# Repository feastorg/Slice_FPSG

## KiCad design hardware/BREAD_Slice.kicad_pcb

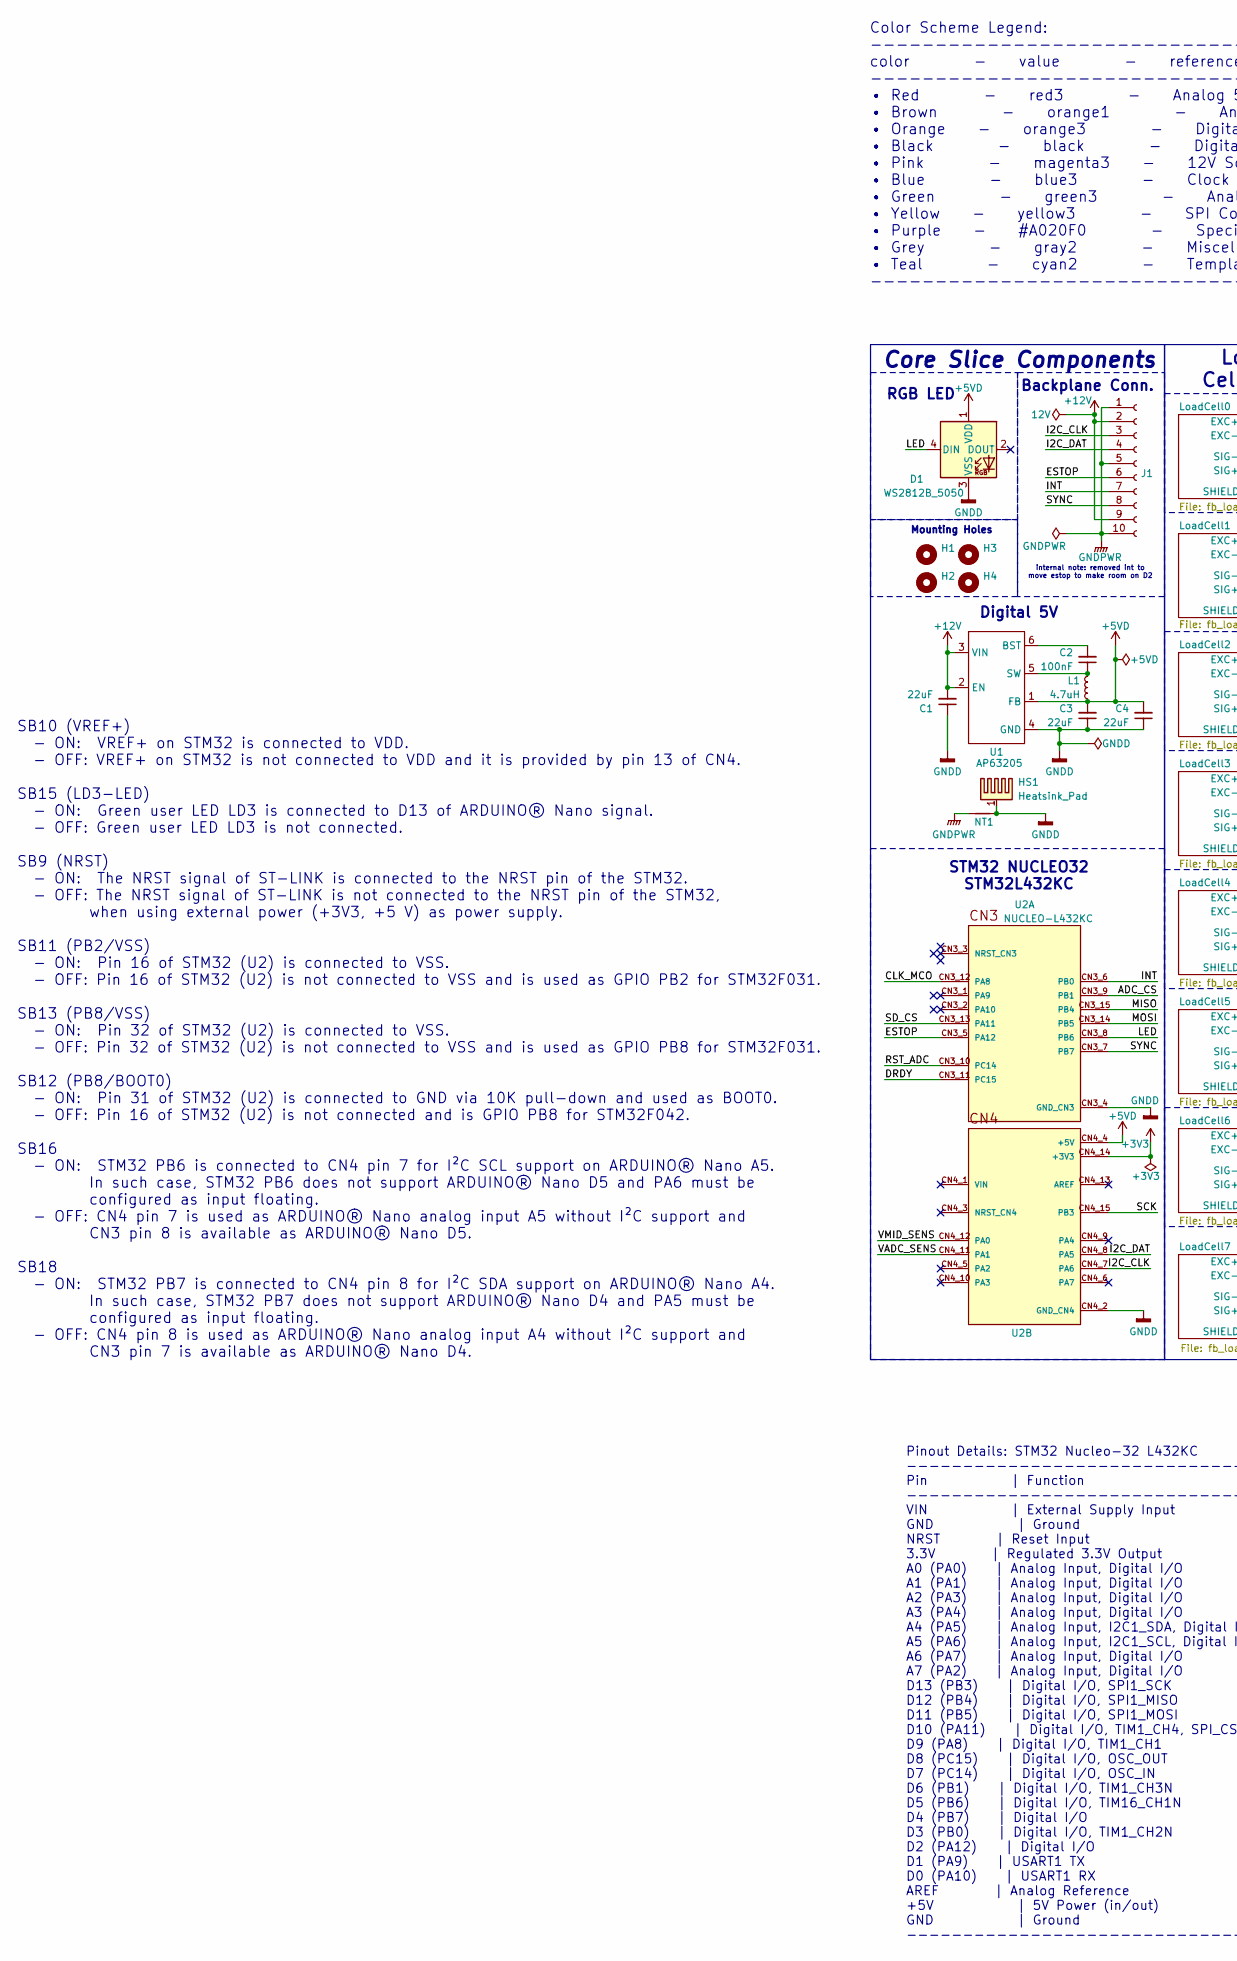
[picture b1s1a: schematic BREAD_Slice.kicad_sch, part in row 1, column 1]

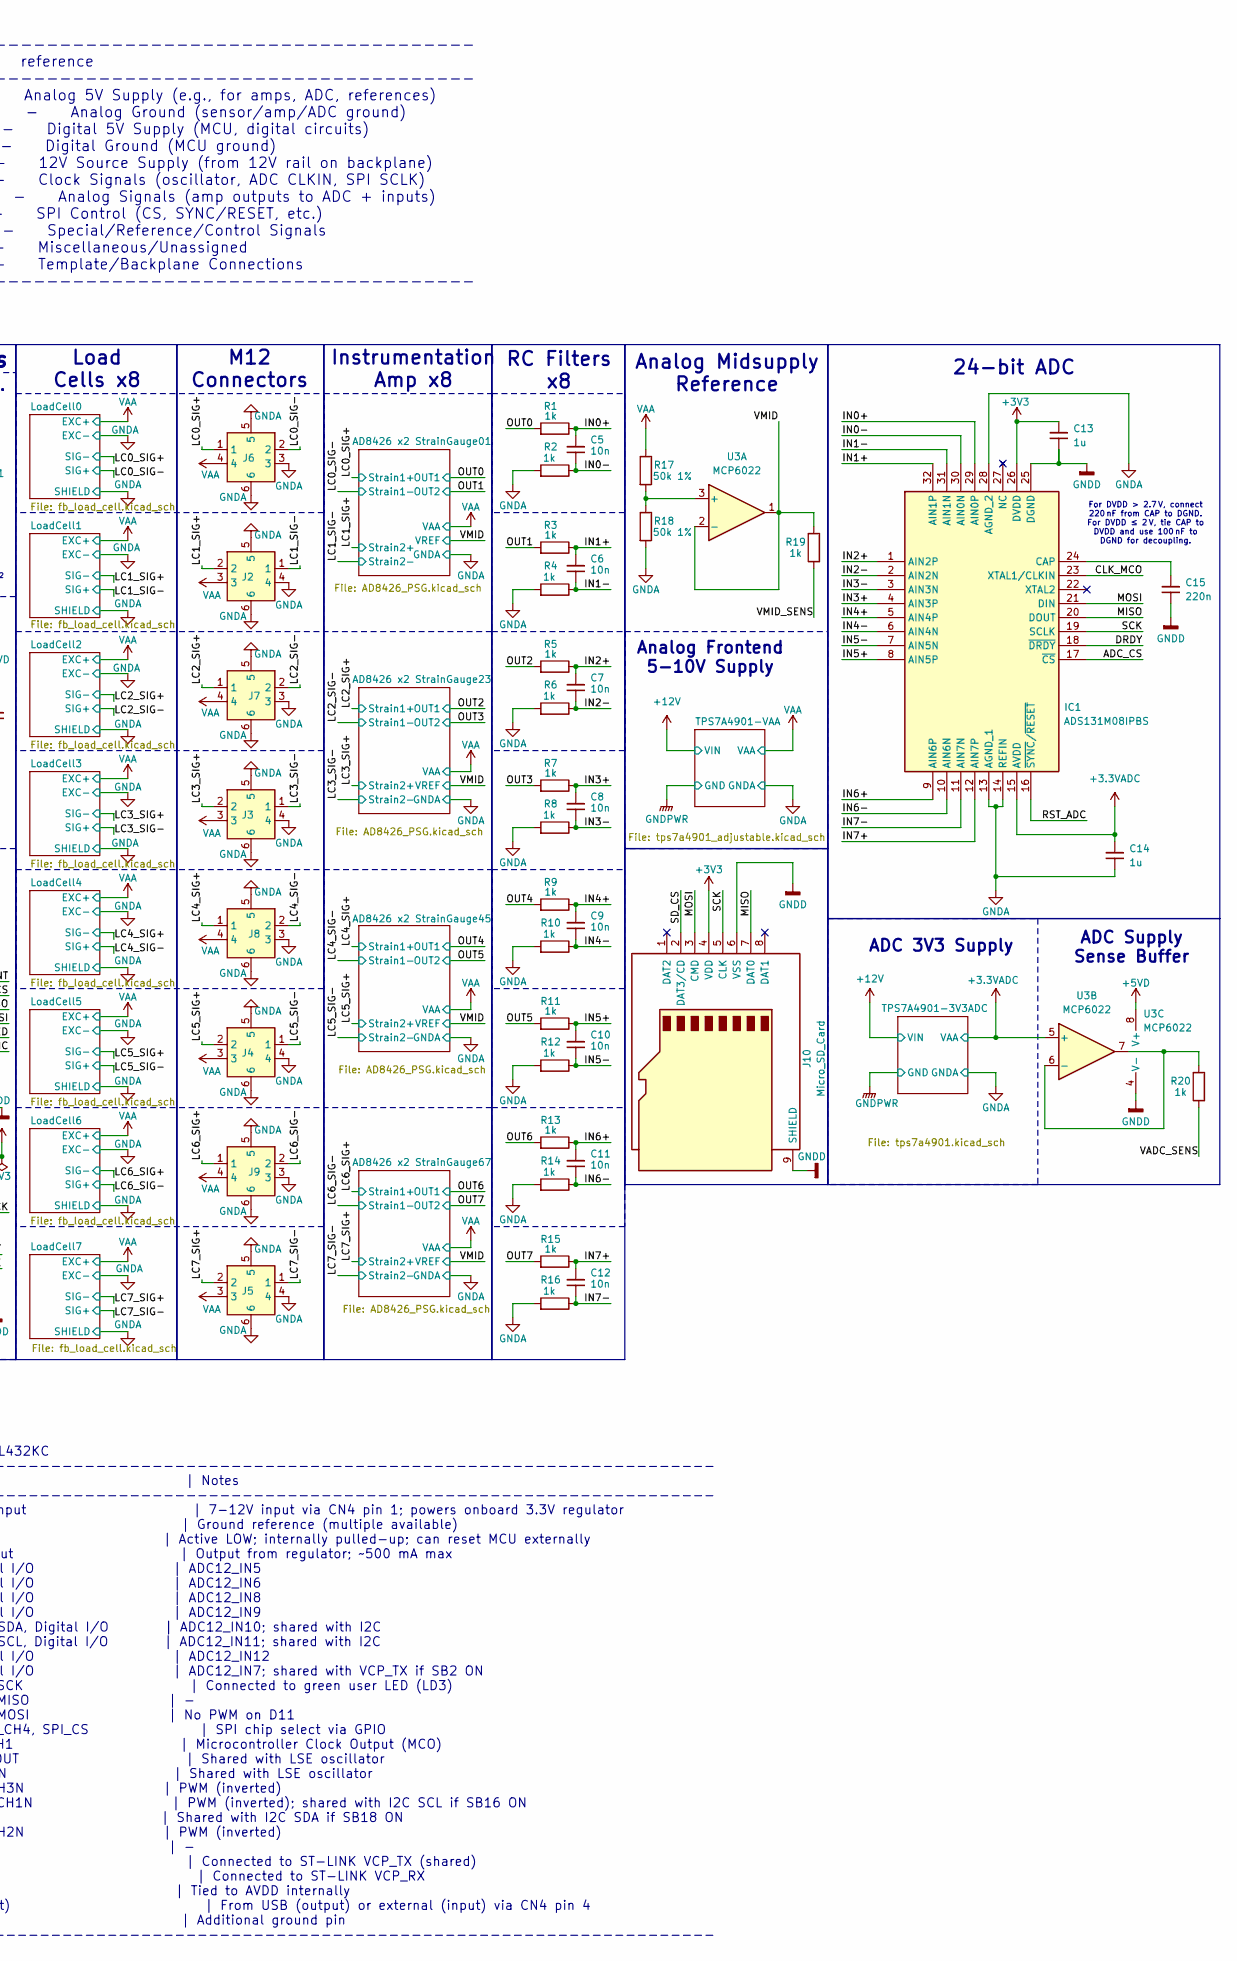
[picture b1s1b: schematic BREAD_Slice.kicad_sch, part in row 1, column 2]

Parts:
C1, C3, C4: 22uF; C_1206_3216Metric
C2: 100nF; C_1206_3216Metric
C5, C6, C7, C8, C9, C10, C11, C12: 10n; C_0805_2012Metric_Pad1.18x1.45mm_HandSolder
C13, C14: 1u; C_1206_3216Metric_Pad1.33x1.80mm_HandSolder
C15: 220n; C_1206_3216Metric_Pad1.33x1.80mm_HandSolder
D1: WS2812B_5050; WS2812-5050-4PIN
H1, H2, H3, H4: MountingHole; MountingHole_5mm
HS1: Heatsink_Pad; Thermal_Pad
IC1: ADS131M08IPBS; QFP50P700X700X120-32N; Mouser Part Number 595-ADS131M08IPBS
J1: Conn_01x10_Female; PinSocket_1x10_P2.54mm_Horizontal
J2, J3, J4, J5, J6, J7, J8, J9: 1439890; Mouser Part Number 651-1439890
J10: Micro_SD_Card; microSD_HC_Molex_47219-2001
L1: 4.7uH; L_1210_3225Metric
NT1: NetTie_2; NetTie-2_SMD_Pad2.0mm
R1, R2, R3, R4, R5, R6, R7, R8, R9, R10, R11, R12, R13, R14, R15, R16, R19, R20: 1k; R_0805_2012Metric_Pad1.20x1.40mm_HandSolder
R17, R18: 50k 1%; R_0805_2012Metric_Pad1.20x1.40mm_HandSolder
U1: AP63205; TSOT-23-6
U2: NUCLEO-L432KC; MODULE_NUCLEO-L432KC; PARTREV N/A
U3: MCP6022; SOIC-8_3.9x4.9mm_P1.27mm

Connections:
+3.3VADC: C14.2, IC1.15 (AVDD), U3.5 (+); also elsewhere on the board
+3V3: C13.2, IC1.26 (DVDD), J10.4 (VDD), U2.CN4_14 (+3V3)
+5VD: C3.2, C4.2, D1.1 (VDD), L1.2, U1.1 (FB), U2.CN4_4 (+5V), U3.8 (V+)
+12V: C1.2, J1.2, J1.9, U1.2 (EN), U1.3 (VIN); also elsewhere on the board
/ADC_CS: IC1.17 (~CS), U2.CN3_9 (PB1)
/CLK_MCO: IC1.23 (XTAL1/CLKIN), U2.CN3_12 (PA8)
/DRDY: IC1.18 (~DRDY), U2.CN3_11 (PC15)
/ESTOP: J1.6, U2.CN3_5 (PA12)
/I2C_CLK: J1.3, U2.CN4_7 (PA6)
/I2C_DAT: J1.4, U2.CN4_8 (PA5)
/IN0+: C5.2, IC1.29 (AIN0P), R1.1
/IN0-: C5.1, IC1.30 (AIN0N), R2.1
/IN1+: C6.2, IC1.32 (AIN1P), R3.1
/IN1-: C6.1, IC1.31 (AIN1N), R4.1
/IN2+: C7.2, IC1.1 (AIN2P), R5.1
/IN2-: C7.1, IC1.2 (AIN2N), R6.1
/IN3+: C8.2, IC1.4 (AIN3P), R7.1
/IN3-: C8.1, IC1.3 (AIN3N), R8.1
/IN4+: C9.2, IC1.5 (AIN4P), R9.1
/IN4-: C9.1, IC1.6 (AIN4N), R10.1
/IN5+: C10.2, IC1.8 (AIN5P), R11.1
/IN5-: C10.1, IC1.7 (AIN5N), R12.1
/IN6+: C11.2, IC1.9 (AIN6P), R13.1
/IN6-: C11.1, IC1.10 (AIN6N), R14.1
/IN7+: C12.2, IC1.12 (AIN7P), R15.1
/IN7-: C12.1, IC1.11 (AIN7N), R16.1
/INT: J1.7, U2.CN3_6 (PB0)
/LC0_SIG+: J6.1; also elsewhere on the board
/LC0_SIG-: J6.2; also elsewhere on the board
/LC1_SIG+: J2.2; also elsewhere on the board
/LC1_SIG-: J2.1; also elsewhere on the board
/LC2_SIG+: J7.1; also elsewhere on the board
/LC2_SIG-: J7.2; also elsewhere on the board
/LC3_SIG+: J3.2; also elsewhere on the board
/LC3_SIG-: J3.1; also elsewhere on the board
/LC4_SIG+: J8.1; also elsewhere on the board
/LC4_SIG-: J8.2; also elsewhere on the board
/LC5_SIG+: J4.2; also elsewhere on the board
/LC5_SIG-: J4.1; also elsewhere on the board
/LC6_SIG+: J9.1; also elsewhere on the board
/LC6_SIG-: J9.2; also elsewhere on the board
/LC7_SIG+: J5.2; also elsewhere on the board
/LC7_SIG-: J5.1; also elsewhere on the board
/LED: D1.4 (DIN), U2.CN3_8 (PB6)
/MISO: IC1.20 (DOUT), J10.7 (DAT0), U2.CN3_15 (PB4)
/MOSI: IC1.21 (DIN), J10.3 (CMD), U2.CN3_14 (PB5)
/OUT0: R1.2; also elsewhere on the board
/OUT1: R3.2; also elsewhere on the board
/OUT2: R5.2; also elsewhere on the board
/OUT3: R7.2; also elsewhere on the board
/OUT4: R9.2; also elsewhere on the board
/OUT5: R11.2; also elsewhere on the board
/OUT6: R13.2; also elsewhere on the board
/OUT7: R15.2; also elsewhere on the board
/RST_ADC: IC1.16 (~SYNC/~RESET), U2.CN3_10 (PC14)
/SCK: IC1.19 (SCLK), J10.5 (CLK), U2.CN4_15 (PB3)
/SD_CS: J10.2 (DAT3/CD), U2.CN3_13 (PA11)
/SYNC: J1.8, U2.CN3_7 (PB7)
/VADC_SENS: R20.2, U2.CN4_11 (PA1)
/VMID: R19.1, U3.1, U3.2 (-); also elsewhere on the board
/VMID_SENS: R19.2, U2.CN4_12 (PA0)
GNDA: C14.1, IC1.13 (AGND_1), IC1.14 (REFIN), IC1.28 (AGND_2), J2.4, J2.5, J2.6, J3.4, J3.5, J3.6, J4.4, J4.5, J4.6, J5.4, J5.5, J5.6, J6.3, J6.5, J6.6, J7.3, J7.5, J7.6, J8.3, J8.5, J8.6, J9.3, J9.5, J9.6, R2.2, R4.2, R6.2, R8.2, R10.2, R12.2, R14.2, R16.2, R18.2; also elsewhere on the board
GNDD: C1.1, C3.1, C4.1, C13.1, C15.1, D1.3 (VSS), HS1.1, IC1.25 (DGND), J10.6 (VSS), J10.9 (SHIELD), NT1.2, U1.4 (GND), U2.CN3_4 (GND_CN3), U2.CN4_2 (GND_CN4), U3.4 (V-)
GNDPWR: J1.1, J1.5, J1.10, NT1.1; also elsewhere on the board
unnamed: C15.2, IC1.24 (CAP)
unnamed: C2.2, U1.6 (BST)
unnamed: C2.1, L1.1, U1.5 (SW)
unnamed: R17.2, R18.1, U3.3 (+)
unnamed: R20.1, U3.6 (-), U3.7
VAA: J2.3, J3.3, J4.3, J5.3, J6.4, J7.4, J8.4, J9.4, R17.1; also elsewhere on the board

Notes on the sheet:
Digital 5V
RC Filters x8
Instrumentation Amp x8
Analog Frontend 5-10V Supply
RGB LED
Pinout Details: STM32 Nucleo-32 L432KC ------------------------------------------------------------------------------------- Pin | Function | Notes ------------------------------------------------------------------------------------- VIN | External Supply Input | 7-12V input via CN4 pin 1; powers o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
Load Cells x8
internal note: removed int to move estop to make room on D2
Color Scheme Legend: ---------------------------------------------------------- color - value - reference ---------------------------------------------------------- • Red - red3 - Analog 5V Supply (e.g., for amps, ADC, references) • Brown - orange1 - Analog Ground (sensor/amp/ADC ground) • Orange -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
Analog Midsupply Reference
SB10 (VREF+) - ON: VREF+ on STM32 is connected to VDD. - OFF: VREF+ on STM32 is not connected to VDD and it is provided by pin 13 of CN4. SB15 (LD3-LED) - ON: Green user LED LD3 is connected to D13 of ARDUINO® Nano signal. - OFF: Green user LED LD3 is not connected. SB9 (NRST) - ON: The NRST signal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
M12 Connectors
Core Slice Components
For DVDD > 2.7 V, connect 220 nF from CAP to DGND. For DVDD ≤ 2 V, tie CAP to DVDD and use 100 nF to DGND for decoupling.
ADC Supply Sense Buffer
STM32 NUCLEO32 STM32L432KC
24-bit ADC
ADC 3V3 Supply
Mounting Holes
Backplane Conn.

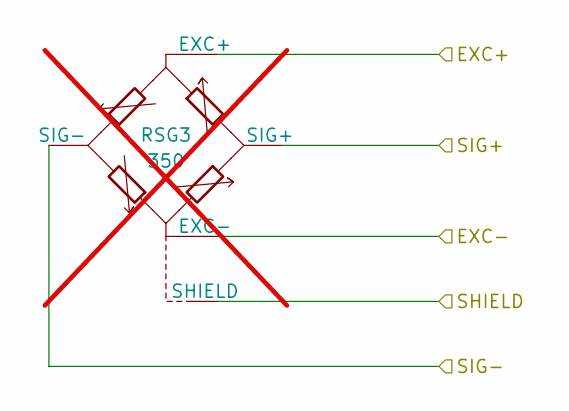
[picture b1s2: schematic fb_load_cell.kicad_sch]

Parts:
RSG3: 350; not fitted

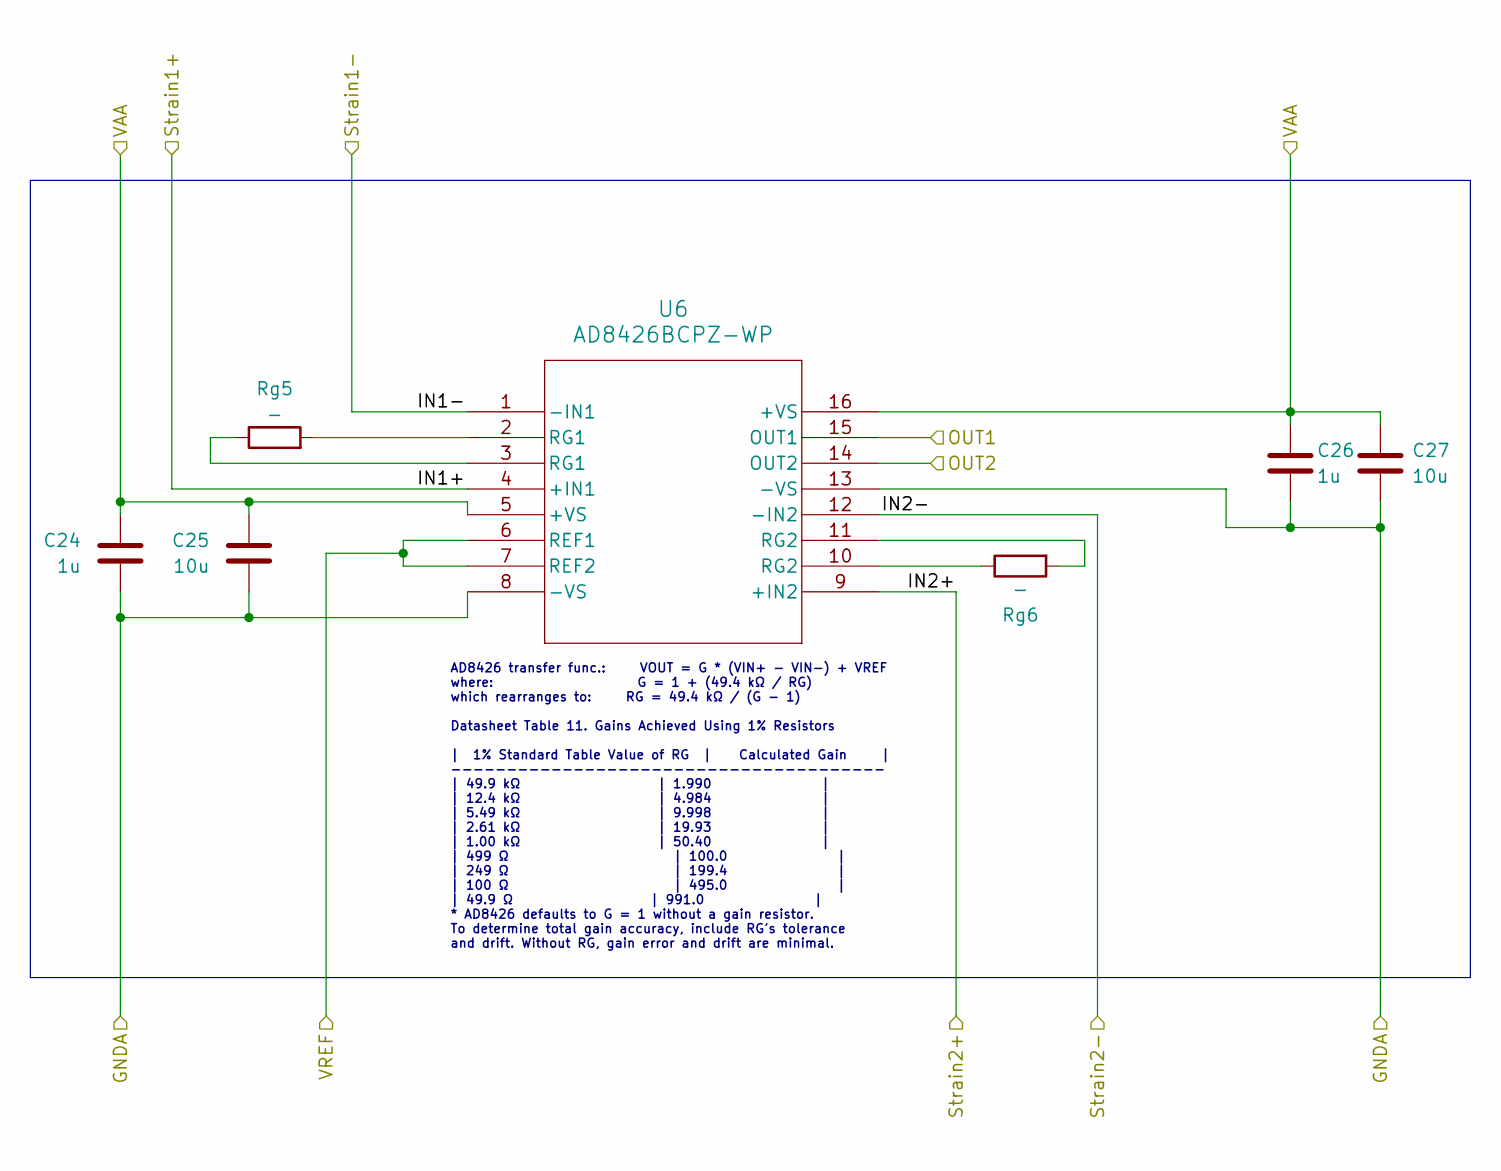
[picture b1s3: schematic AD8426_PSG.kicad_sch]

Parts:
C24, C26: 1u; C_0603_1608Metric_Pad1.08x0.95mm_HandSolder
C25, C27: 10u; C_0603_1608Metric_Pad1.08x0.95mm_HandSolder
Rg5, Rg6: -; R_0805_2012Metric_Pad1.20x1.40mm_HandSolder
U6: AD8426BCPZ-WP; CP_16_19_ADI

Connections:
/LC4_SIG+: U6.4 (+IN1); also elsewhere on the board
/LC4_SIG-: U6.1 (-IN1); also elsewhere on the board
/LC5_SIG+: U6.9 (+IN2); also elsewhere on the board
/LC5_SIG-: U6.12 (-IN2); also elsewhere on the board
/OUT4: U6.15 (OUT1); also elsewhere on the board
/OUT5: U6.14 (OUT2); also elsewhere on the board
/VMID: U6.6 (REF1), U6.7 (REF2); also elsewhere on the board
GNDA: C24.2, C25.2, C26.2, C27.2, U6.8 (-VS), U6.13 (-VS); also elsewhere on the board
unnamed: Rg5.1, U6.3 (RG1)
unnamed: Rg5.2, U6.2 (RG1)
unnamed: Rg6.1, U6.10 (RG2)
unnamed: Rg6.2, U6.11 (RG2)
VAA: C24.1, C25.1, C26.1, C27.1, U6.5 (+VS), U6.16 (+VS); also elsewhere on the board

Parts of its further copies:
C16, C18, C20, C22, C28, C30: 1u; C_0603_1608Metric_Pad1.08x0.95mm_HandSolder
C17, C19, C21, C23, C29, C31: 10u; C_0603_1608Metric_Pad1.08x0.95mm_HandSolder
Rg1, Rg2, Rg3, Rg4, Rg7, Rg8: -; R_0805_2012Metric_Pad1.20x1.40mm_HandSolder
U4, U5, U7: AD8426BCPZ-WP; CP_16_19_ADI

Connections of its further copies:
/LC0_SIG+: U4.4 (+IN1); also elsewhere on the board
/LC0_SIG-: U4.1 (-IN1); also elsewhere on the board
/LC1_SIG+: U4.9 (+IN2); also elsewhere on the board
/LC1_SIG-: U4.12 (-IN2); also elsewhere on the board
/LC2_SIG+: U5.4 (+IN1); also elsewhere on the board
/LC2_SIG-: U5.1 (-IN1); also elsewhere on the board
/LC3_SIG+: U5.9 (+IN2); also elsewhere on the board
/LC3_SIG-: U5.12 (-IN2); also elsewhere on the board
/LC6_SIG+: U7.4 (+IN1); also elsewhere on the board
/LC6_SIG-: U7.1 (-IN1); also elsewhere on the board
/LC7_SIG+: U7.9 (+IN2); also elsewhere on the board
/LC7_SIG-: U7.12 (-IN2); also elsewhere on the board
/OUT0: U4.15 (OUT1); also elsewhere on the board
/OUT1: U4.14 (OUT2); also elsewhere on the board
/OUT2: U5.15 (OUT1); also elsewhere on the board
/OUT3: U5.14 (OUT2); also elsewhere on the board
/OUT6: U7.15 (OUT1); also elsewhere on the board
/OUT7: U7.14 (OUT2); also elsewhere on the board
/VMID: U4.6 (REF1), U4.7 (REF2), U5.6 (REF1), U5.7 (REF2), U7.6 (REF1), U7.7 (REF2); also elsewhere on the board
GNDA: C16.2, C17.2, C18.2, C19.2, C20.2, C21.2, C22.2, C23.2, C28.2, C29.2, C30.2, C31.2, U4.8 (-VS), U4.13 (-VS), U5.8 (-VS), U5.13 (-VS), U7.8 (-VS), U7.13 (-VS); also elsewhere on the board
unnamed: Rg1.1, U4.3 (RG1)
unnamed: Rg1.2, U4.2 (RG1)
unnamed: Rg2.1, U4.10 (RG2)
unnamed: Rg2.2, U4.11 (RG2)
unnamed: Rg3.1, U5.3 (RG1)
unnamed: Rg3.2, U5.2 (RG1)
unnamed: Rg4.1, U5.10 (RG2)
unnamed: Rg4.2, U5.11 (RG2)
unnamed: Rg7.1, U7.3 (RG1)
unnamed: Rg7.2, U7.2 (RG1)
unnamed: Rg8.1, U7.10 (RG2)
unnamed: Rg8.2, U7.11 (RG2)
VAA: C16.1, C17.1, C18.1, C19.1, C20.1, C21.1, C22.1, C23.1, C28.1, C29.1, C30.1, C31.1, U4.5 (+VS), U4.16 (+VS), U5.5 (+VS), U5.16 (+VS), U7.5 (+VS), U7.16 (+VS); also elsewhere on the board

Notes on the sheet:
AD8426 transfer func.: VOUT = G * (VIN+ - VIN-) + VREF where: G = 1 + (49.4 kΩ / RG) which rearranges to: RG = 49.4 kΩ / (G - 1) Datasheet Table 11. Gains Achieved Using 1% Resistors | 1% Standard Table Value of RG | Calculated Gain | --------------------------------------- | 49.9 kΩ | 1.990 | | 12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

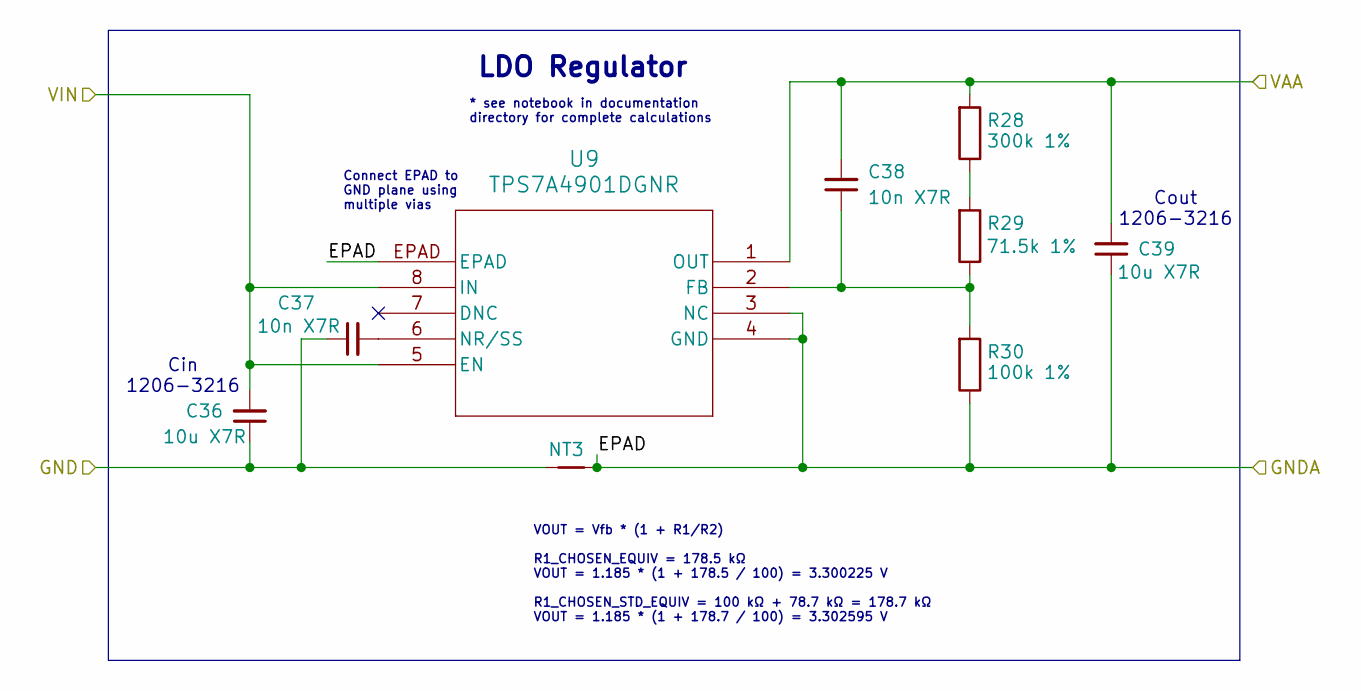
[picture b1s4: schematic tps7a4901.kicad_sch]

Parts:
C36, C39: 10u X7R; C_1206_3216Metric_Pad1.33x1.80mm_HandSolder
C37, C38: 10n X7R; C_0603_1608Metric_Pad1.08x0.95mm_HandSolder
NT3: NetTie_2; NetTie-2_SMD_Pad2.0mm
R28: 300k 1%; R_0805_2012Metric_Pad1.20x1.40mm_HandSolder
R29: 71.5k 1%; R_0805_2012Metric_Pad1.20x1.40mm_HandSolder
R30: 100k 1%; R_0805_2012Metric_Pad1.20x1.40mm_HandSolder
U9: TPS7A4901DGNR; DGN8_1P89X1P57

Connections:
+3.3VADC: C38.2, C39.2, R28.2, U9.1 (OUT); also elsewhere on the board
+12V: C36.2, U9.5 (EN), U9.8 (IN); also elsewhere on the board
GNDA: C39.1, NT3.2, R30.1, U9.3 (NC), U9.4 (GND), U9.EPAD; also elsewhere on the board
GNDPWR: C36.1, C37.1, NT3.1; also elsewhere on the board
unnamed: R28.1, R29.2
unnamed: C38.1, R29.1, R30.2, U9.2 (FB)
unnamed: C37.2, U9.6 (NR/SS)

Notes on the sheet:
Cin 1206-3216
LDO Regulator
Cout 1206-3216
* see notebook in documentation directory for complete calculations
VOUT = Vfb * (1 + R1/R2) R1_CHOSEN_EQUIV = 178.5 kΩ VOUT = 1.185 * (1 + 178.5 / 100) = 3.300225 V R1_CHOSEN_STD_EQUIV = 100 kΩ + 78.7 kΩ = 178.7 kΩ VOUT = 1.185 * (1 + 178.7 / 100) = 3.302595 V
Connect EPAD to GND plane using multiple vias

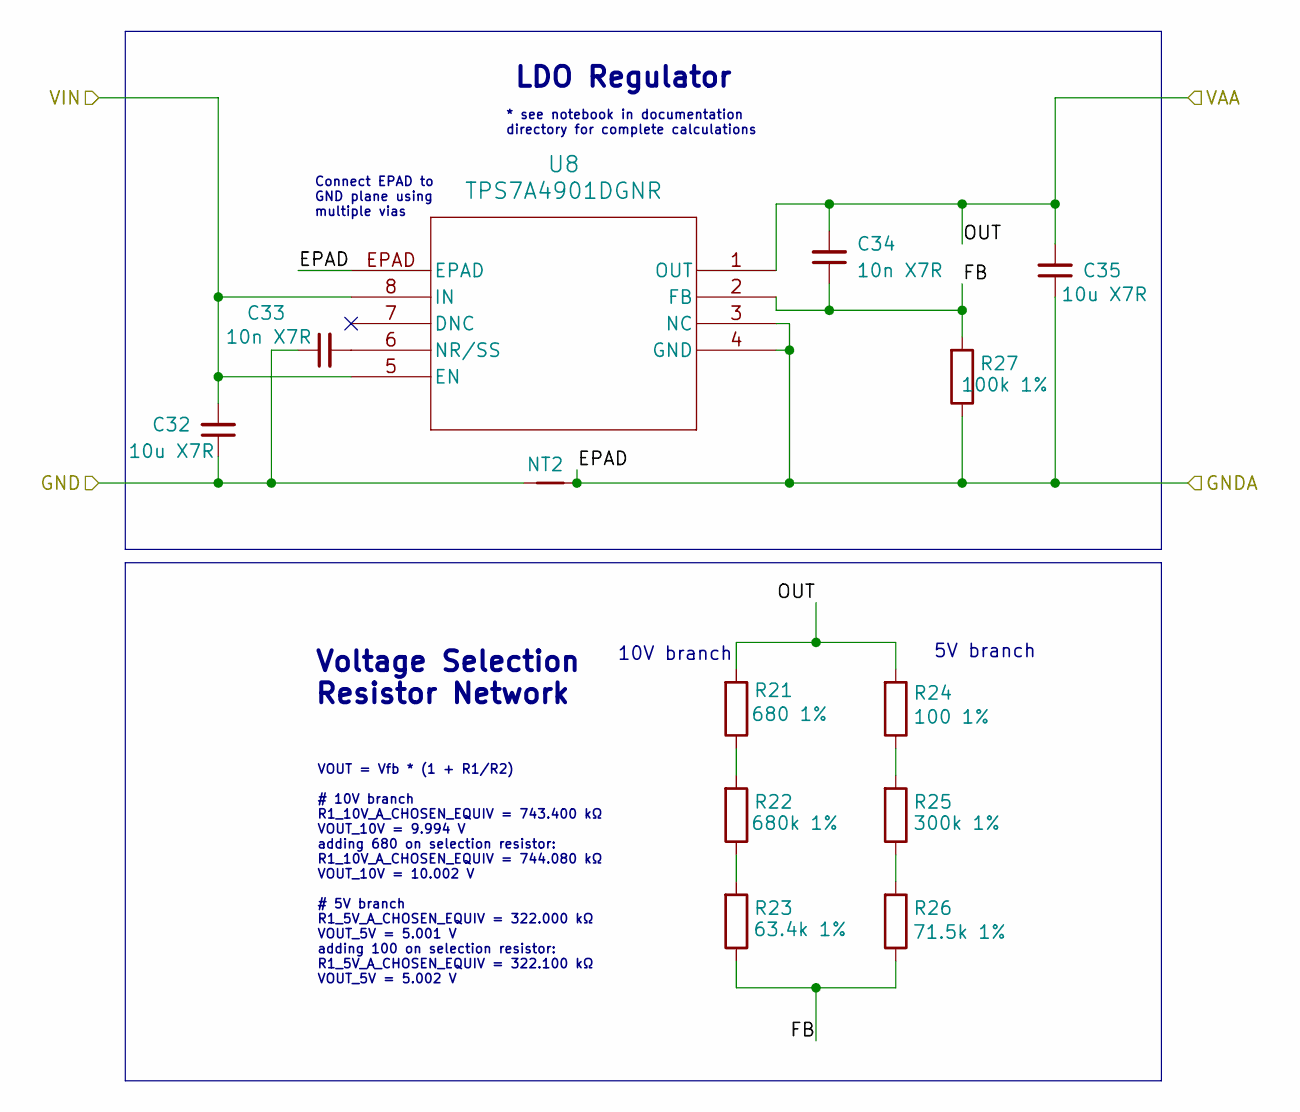
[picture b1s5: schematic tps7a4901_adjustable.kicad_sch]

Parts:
C32, C35: 10u X7R; C_1206_3216Metric_Pad1.33x1.80mm_HandSolder
C33, C34: 10n X7R; C_0603_1608Metric_Pad1.08x0.95mm_HandSolder
NT2: NetTie_2; NetTie-2_SMD_Pad2.0mm
R21: 680 1%; R_0805_2012Metric_Pad1.20x1.40mm_HandSolder
R22: 680k 1%; R_0805_2012Metric_Pad1.20x1.40mm_HandSolder
R23: 63.4k 1%; R_0805_2012Metric_Pad1.20x1.40mm_HandSolder
R24: 100 1%; R_0805_2012Metric_Pad1.20x1.40mm_HandSolder
R25: 300k 1%; R_0805_2012Metric_Pad1.20x1.40mm_HandSolder
R26: 71.5k 1%; R_0805_2012Metric_Pad1.20x1.40mm_HandSolder
R27: 100k 1%; R_0805_2012Metric_Pad1.20x1.40mm_HandSolder
U8: TPS7A4901DGNR; DGN8_1P89X1P57

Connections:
+12V: C32.2, U8.5 (EN), U8.8 (IN); also elsewhere on the board
/TPS7A4901-VAA/FB: C34.1, R23.1, R26.1, R27.2, U8.2 (FB)
GNDA: C35.1, NT2.2, R27.1, U8.3 (NC), U8.4 (GND), U8.EPAD; also elsewhere on the board
GNDPWR: C32.1, C33.1, NT2.1; also elsewhere on the board
unnamed: R21.1, R22.2
unnamed: R22.1, R23.2
unnamed: R24.1, R25.2
unnamed: R25.1, R26.2
unnamed: C33.2, U8.6 (NR/SS)
VAA: C34.2, C35.2, R21.2, R24.2, U8.1 (OUT); also elsewhere on the board

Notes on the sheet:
* see notebook in documentation directory for complete calculations
LDO Regulator
5V branch
VOUT = Vfb * (1 + R1/R2) # 10V branch R1_10V_A_CHOSEN_EQUIV = 743.400 kΩ VOUT_10V = 9.994 V adding 680 on selection resistor: R1_10V_A_CHOSEN_EQUIV = 744.080 kΩ VOUT_10V = 10.002 V # 5V branch R1_5V_A_CHOSEN_EQUIV = 322.000 kΩ VOUT_5V = 5.001 V adding 100 on selection resistor: R1_5V_A_CHOSEN_EQUIV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
Voltage Selection Resistor Network
10V branch
Connect EPAD to GND plane using multiple vias

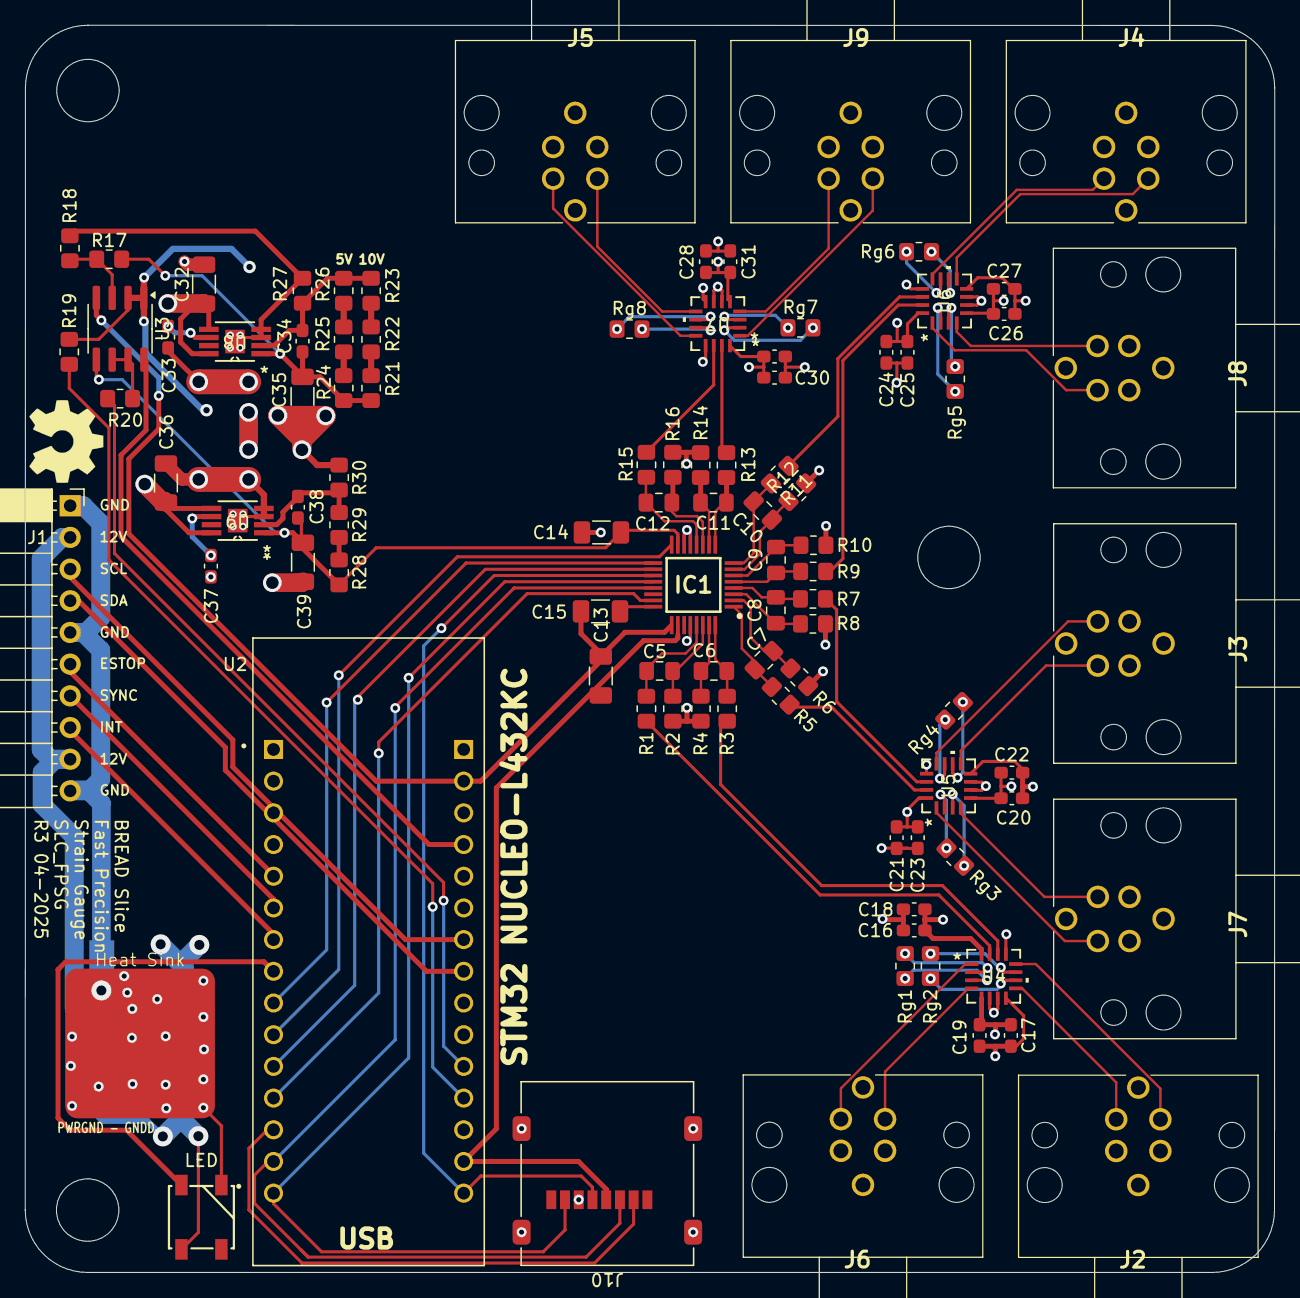
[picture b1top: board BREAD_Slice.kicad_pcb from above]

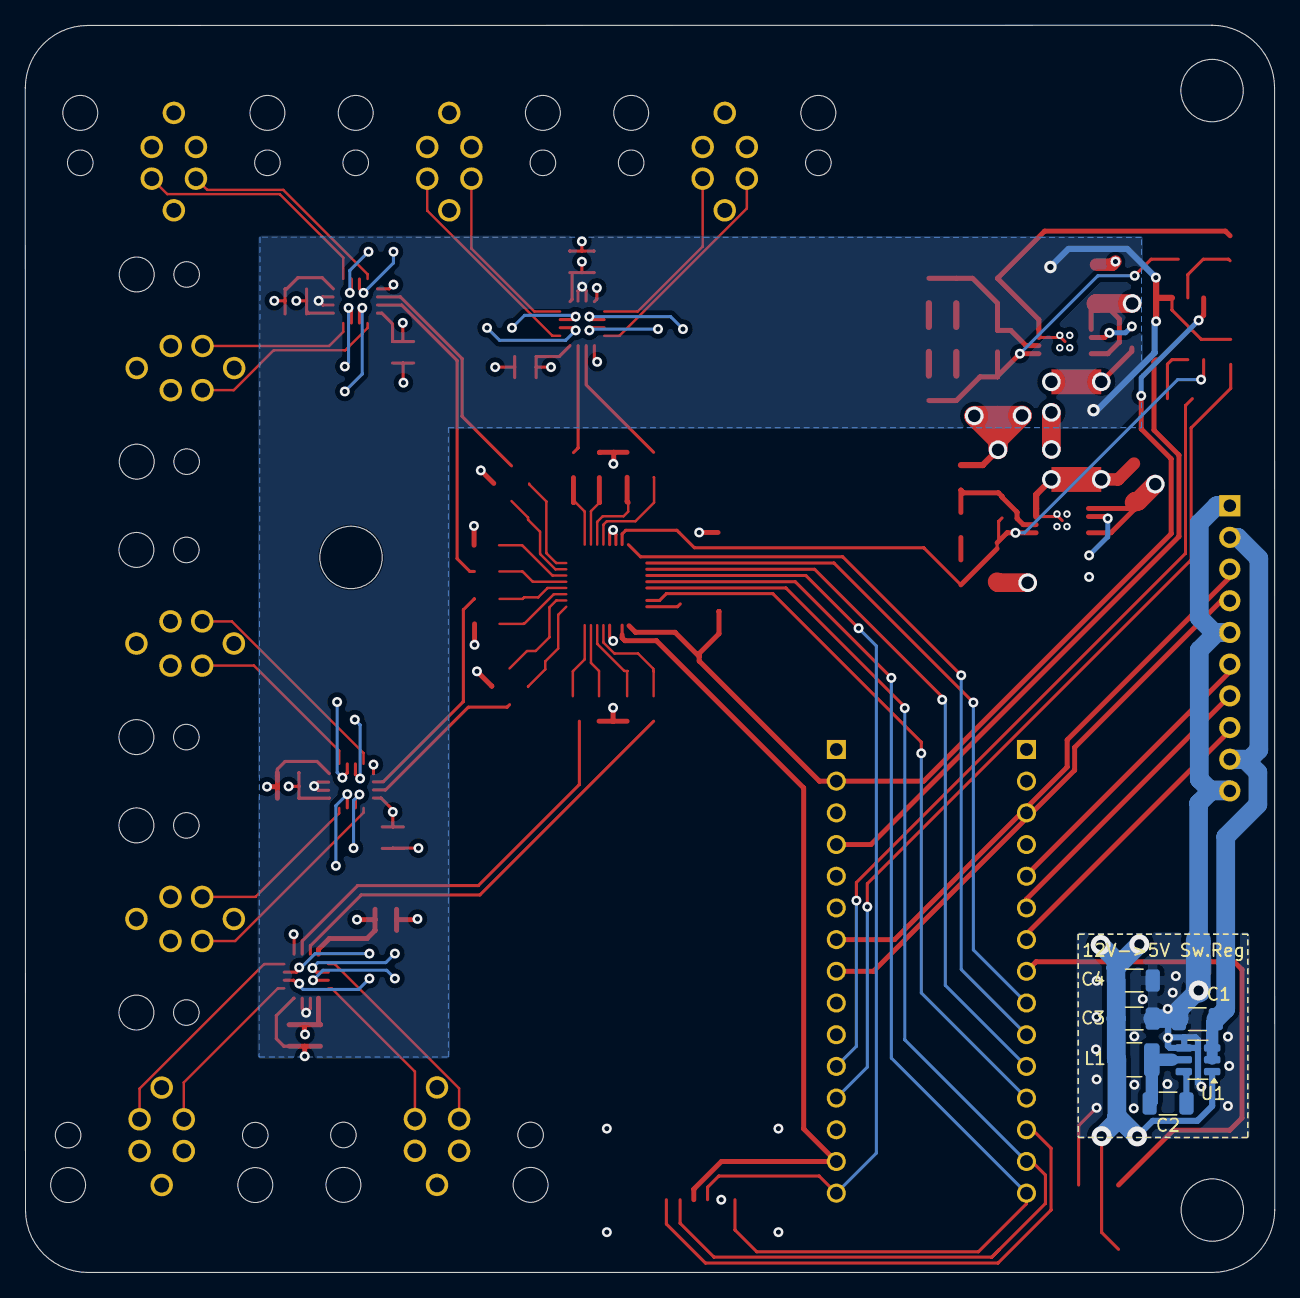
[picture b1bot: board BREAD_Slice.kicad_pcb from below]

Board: 4 copper layers, 100.1 x 100.0 mm, 107 parts (7 on the bottom side), 95 nets.

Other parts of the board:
Logo1: Logo_Open_Hardware_Small; OSHW-Symbol_6.7x6mm_SilkScreen

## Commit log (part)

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2025-04-01 initial commit of hw
2025-04-02 updated some docs
2025-04-02 removed rogue readme
2025-04-10 finalize board before switch to stm
2025-04-12 final iteration of board with proper connectors and clean layout
2025-04-19 added new hw
2026-04-18 chore: export gerbers
2026-05-20 Add slice.yaml manifest (schema v1.0)
2026-05-24 Add KiBot/docs pipeline (4-layer)
2026-05-24 Update TODO with CI findings (DRC errors)
